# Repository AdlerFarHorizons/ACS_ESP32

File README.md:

# ACS_ESP32
### Current State of ACS Development (April 2022)

The Altitude Control System has been updated to work with the ESP32 Microcontroller which has enabled wireless file sharing via WiFi. The exact module is the **DOIT ESP32 DEVKIT V1**. 

**Firmware**

The [ACS_ESP32 Code](https://github.com/AdlerFarHorizons/ACS_ESP32) has been organized for clarity, usage, and further development. The code now lives publicly within the [Adler Far Horizons GitHub](https://github.com/AdlerFarHorizons). Additionally, the code and the libraries are packaged by the [PlatformIO](https://platformio.org/platformio-ide) package, which runs within [VS Code](https://code.visualstudio.com/), and should be used to maintain and update the code. Cloning the repository from within GitHub will ensure PlatformIO compiles the code properly. 

The following are updates to the code:

- Code has been organized into separate header files (_name_.h) so as to keep all related code for specific peripherals in separate files. This allows the programmer to quickly find specific functions.
- Wireless file retrieval has been added. The microcontroller will broadcast a hotspot with SSID: “ACS SD-CARD”. The SD Card content can be displayed by entering the IP-ADDRESS: “192.168.4.1” into a web browser after establishing wifi connection. 

To access wifi settings, 

1. Turn on the ACS by using the Toggle ON/OFF switch or by plugging using a USB cable.

2. Using your computer (or mobile device), look for the “ACS SD-Card” Hotspot under the WIFI settings. You do not need a password to access the hotspot.

3. Identify the 3-position switch on the ACS Faceplate. Place this switch to the Closed Position (or the center position), and Press the Button as indicated on the Display. You should now see the IP Address displayed, which should be “192.168.4.1”.

   1. Sometimes the connection is poor, and you may need to bring the ACS closer to you, or you may need to reestablish the WIFI connection by turning off/on your wireless antenna on your computer/mobile device.

4. If your connection is established, you should now see a window as shown below: 

Within this window you may browse through the content within the SD Card by selecting Directory. If you wish to download a file, you can copy/paste the full name of the file and paste it into the Downloads prompt window. 

The use of WIFI is to be able to download the param.txt file, edit it and upload it back into the ACS SD Card. Additionally, one can download the datalog.csv, which contains all the flight ACS data. Ideally, one should not have to remove the SD Card from the board. 

__Note: I’ve noticed that deleting a file via WIFI sends it to the .Trash Folder. It doesn’t fully delete the file. So when the script runs and looks for a file within the list of files, if the file exists within the .Trash folder, then the code will send a True that the file exists. The code either needs a exception to not search within .Trash or a “Permanently Delete” function that deletes the content within .Trash.__

### Design Files, Notes, and Code

[GitHub - ACS_ESP32](https://github.com/AdlerFarHorizons/ACS_ESP32)

[Google Drive: System Redesign Concept 2021/22](https://drive.google.com/drive/folders/1W37AFGbH8UgUThIRDDYVn1NRzvqxMLDn)

- [PCB Design Files](https://drive.google.com/drive/folders/1NPGxpG3kCgMrHuZ5ZHsxEYcvnIpvRIrO?usp=sharing)
- [PCB Schematic PDF](https://drive.google.com/file/d/19PMDI1tQQiT3bByivIbot_-rFZreG9Ll/view?usp=sharing)

[Purchase Materials****](https://docs.google.com/spreadsheets/d/1xs60UxvHJ-fiQykCOm7pP0R7RBD7VAjFjShzD04MD6w/edit#gid=0)

**Compiling using Arduino**

To compile and upload the script file using Arduino, you must install the ESP32 Arduino Boards using instructions found here.

**Instructions**: [Installing ESP32 in Arduino IDE](https://randomnerdtutorials.com/installing-the-esp32-board-in-arduino-ide-windows-instructions/) 

Upon Install, select the **DOIT ESP32 DEVKIT V1 **Board from the drop down menu within **Tools/Board/ESP32 Arduino/. **The this dropdown menu is shown below:

**Printed Circuit Board (PCB)**

The PCB for the ACS has had several modifications. Primarily, the Teensy 3.6 Microcontroller has been exchanged for the WIFI capable microcontroller [**ESP-WROOM-32 ESP-32S Development Board**](https://www.amazon.com/dp/B08D5ZD528?psc=1&ref=ppx_yo2ov_dt_b_product_details)**. **This microcontroller does not include an SD Card Reader, which is why an [SD Card Reader Breakout Board](https://www.sparkfun.com/products/13743) has been added to the new design. 

In addition to the microcontroller modifications, the PCB now utilizes a few surface-mounted devices. 

- **Power**: The previous design used the [LM7805 Voltage Regulator](https://www.sparkfun.com/datasheets/Components/LM7805.pdf) which dropped the 7.2V to 5V using a conventional heat dissipation voltage regulator. This approach worked, but consumed much higher current draw. Therefore, the DC-DC voltage regulator was exchanged for a low-dropout voltage regulator. The selected voltage regulator is now the [MC33269](https://www.onsemi.com/pdf/datasheet/mc33269-d.pdf). 
- **Logic Level Shifter: The original [4-channel I2C-safe Bi-directional Logic Level Converter - BSS138](https://www.adafruit.com/product/757) has been stripped down to only use 1 of the [BSS138](https://www.onsemi.com/pdf/datasheet/bss138-d.pdf) configured to convert signals from low voltage 3V3 to 5.0 Volts.**
- **Actuator**: The current actuator is the L12-50-210-6-R, which runs a servo motor to extend the actuator. However, this actuator does not provide feedback positional data, therefore the recommendation is to upgrade the actuator to the [**L12-50-210-6-I**](https://s3.amazonaws.com/actuonix/Actuonix+L12+Datasheet.pdf)**. **The L12-I version contains an integrated microcontroller which allows the user to obtain positional feedback data. 

**Connection Diagram**

**AA Battery Set for Actuator + Primary Board**

The current AA battery set used in the ACS is the [ Xeno XL-060F AA 2400mAh 3.6V Lithium Thionyl Chloride (LiSOCI2)](https://www.batteryjunction.com/xl-060f-xeno-aa.html) \[[datasheet](https://files.batteryjunction.com/frontend/files/xeno/datasheet/Xeno-XL-060F-Datasheet.pdf)], which is placed in Series to increase the voltage to 7.2. The ACS uses four (4) AA Batteries - 2 sets in Series, and those two sets are merged in parallel to increase the capacity (mAh).

**External Temperature Battery Board**

This board has been prepared to connect to the primary board, but is placed separately from it in order to be close enough to the heating elements for it to monitor temperatures and hold the two 9V batteries to power the heating element.

- **Temperature:** The temperature is monitored using a [DS18B20 Digital Thermometer](https://datasheets.maximintegrated.com/en/ds/DS18B20.pdf).
- **Batteries:** The 9V batteries are held in place by both the structure of the compartment it will reside in and power the heating through two [5331TR (Leaf-Spring Battery Contacts)](https://www.digikey.com/en/products/detail/keystone-electronics/5331TR/8347168?utm_adgroup=General&utm_source=google&utm_medium=cpc&utm_campaign=Smart%20Shopping_Product_Zombie%20SKUS&utm_term=&utm_content=General&gclid=CjwKCAiAprGRBhBgEiwANJEY7DhVwsQ1aTq7gBAcb5RRHrVmZTxuCmMAlXrXpHnIgzOPE_fwFTYqjRoCqlUQAvD_BwE) each. These battery contacts serve a dual purpose as the screws that will go through them are the same ones being used to mount the board securely.
- **Connection: The board is connected to the primary one using a 5 Pin [Screw Terminal Block](https://www.pololu.com/product/2493) affixed to the bottom of the board which will allow wires to be led through a hole beneath it on the way to the main board.**

****

### NEXT TASKS

**Actuator**

- After providing 6.5V to the L-12-I actuator via the DC-Power Supply, **ensure the actuator responds correctly to the ACS_ESP32 Code**. If it does not respond correctly, change the RC_INPUT_SIG Pin to another pin on the ESP32. I’ve identified that some of the pins on the ESP32 seem to short out the microcontroller and/or do not behave as intended. On the code, navigate to actuator.h and find line “**int actuator_pin = 17;”.** Test out a different GPIO pio, upload code, and test for actuator response. 

  - If the actuator ‘jerks’ back and forth when attempting to reach a certain position, the datasheet recommends to “place a 1–4Ω resistor in series with the actuator’s red V+ lead wire”.

- **Actuator Feedback** via the POS_FEEDBACK_SIG pin, which has been connected to GPIO13, must be checked for incoming data. After declaring the POS_FEEDBACK_PIN as an int, use pinMode(POS_FEEDBACK_PIN, INPUT); to initialize the pin on the microcontroller, one should be able to read the voltage using the analogRead() function. One should expect a voltage reading from 0-255, which then can be mapped using map() to correspond to a percentage. 

- Actuator Pins CURR_INPUT_SIG and VOLT_INPUT_SIG have purposefully been disconnected from the microcontroller. These features for controlling the actuator are unnecessary as the actuator will be controlled via the RC_INPUT_SIG.

**The Heating Element**

- The Heating Element needs to be tested the new downsize of voltage output. Originally the heating element uses 3 batteries in series of 9V totalling 27V. Now, the downsize should yield 18V. This downsize has been considered given the usage of an aluminum pipe for heat distribution. 
- Code: Create Algorithm to measure heat transfer between the heating element and the internal electronics, by measuring the temperature outside the heating element (battery board) and the internal Pressure Sensor thermometer. Using these temperatures, create a function that activates the heating element below a specific temperature, and conversely deactivates the heating element when temperatures reach a specific maximum. 
- Heating Element Transistor 2N2222 schematic needs to be tested prior to finalizing the schematic design of the primary board. 

Above: Circuit concept idea for the resistor being the heating element connected to one end of the transistor 2N2222.

Above: Schematic capture of the heating element connector. Here the heating element is connected to one side of the NPN transistor. The Base is connected to the microController, and the Collector is connected to the negative end of the 9V battery set, which is connected in series. 

**Code**

Within the void setup() function, ensure that when the sd_setup() does not create a new file each time the boot process occurs. The ACS should conserve and append the currently existing logfile if it exists. If the file does not exist, the code is instructed to write the parameters below:

else
{ unsigned long size = logFile.size();
  Serial.print("Filesize: "); Serial.println(size);
  delay(5000);
  if (size < 500){
    display.clearDisplay();
    display.println("Creating new File");
    display.display();
    delay(5000);

    String log = 
                "Far Horizons | Adler Planetarium" + String("\n") + 
                "Flight Number: " + "," +            String(flightNum) + "\n" + 
                "Firmware: " + "," +                  String(the_sketchname) + "\n" + 
                "Compiled on: " +  "," +               String(__DATE__) +  " at " +  String(__TIME__) + "\n" +
                "Venting Altitude (m): " + "," +      String(VENT_ALT) + "\n" + 
                "Float Time (min): " + "," +          String(FLOAT_TIME) + "\n" + 
                "Max Float Altitude (m): " + "," +   String(MAXFLOATALT) + "\n" + 
                "Release Position %: " + "," +        String(RELEASE_POS) + "\n" + 
                "Venting Position %: " + "," +        String(OPEN_POS) + "," + 
                "Closed Position" + "," + String(CLOSED_POS) + "\n";

Currently this section of the code does not work as intended. Instead, the code creates a new file and does not append the parameters found above.

**ACS Primary PCB**

- Label Pins on Connectors using layer tNames and bNames.
- Ensure Connector are placed in the correct location to help diminish excess wire routing and unnecessary wire-curvatures.
- Rework routes after device placement and use ratsnest to create the correct ground plane

**Currently Wired Diagram on Breadboard: **

**Full Schematic Diagram with External Temp Board**

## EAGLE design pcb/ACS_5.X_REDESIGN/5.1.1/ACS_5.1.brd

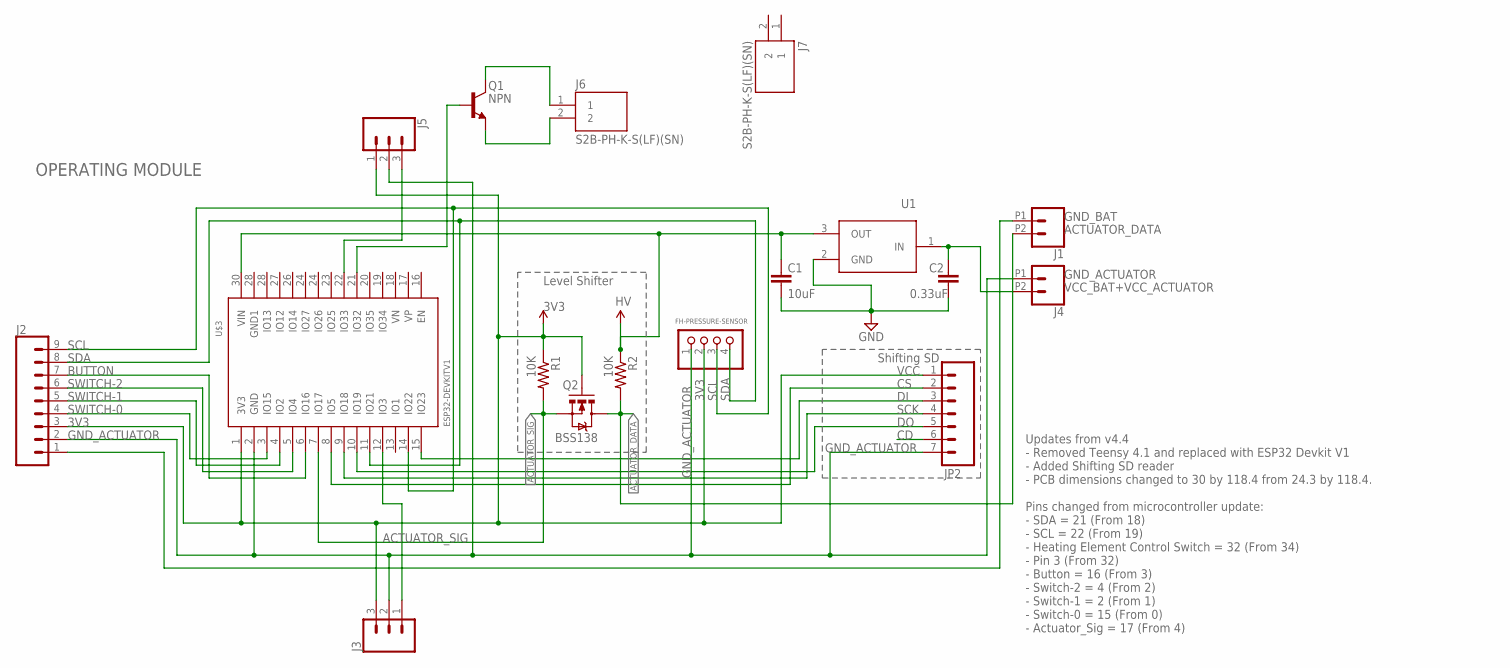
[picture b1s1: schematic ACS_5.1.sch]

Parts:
C1: 10uF; CAPC1608X85
C2: 0.33uF; CAPC1608X85
FH-PRESSURE-SENSOR: PINHD-1X4; 1X04
J1, J4: CONN_022.54MM_SCREWTERM; 1X02_2.54_SCREWTERM
J2: CONN_09; 1X09
J3, J5: CONN_03; 1X03
J6, J7: S2B-PH-K-S(LF)(SN); JST_S2B-PH-K-S(LF)(SN)
JP2: M07; 1X07
Q1: NPN; SOT95P237X112-3N
Q2: BSS138; SOT23-3
R1, R2: 10K; 0603-RES
U1: MC78M05BDTRKG
U$3: ESP32DEVKITV1; ESP32-DEVKITV1

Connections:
3V3: FH-PRESSURE-SENSOR.2, J2.3, J3.3, J5.1, JP2.1, Q2.1 (G), R1.1, U$3.1 (3V3)
ACTUATOR_DATA: J1.P2 (2), Q2.3 (D), R2.2
ACTUATOR_SIG: Q2.2 (S), R1.2, U$3.7 (IO17)
BUTTON: J2.7, U$3.6 (IO16)
GND: C1.2, C2.2, U1.2 (GND)
GND_ACTUATOR: FH-PRESSURE-SENSOR.1, J2.2, J3.2, J4.P1 (1), J5.2, JP2.7, U$3.2 (GND)
GND_BAT: J1.P1 (1), J2.1
HV: C1.1, R2.1, U1.3 (OUT), U$3.30 (VIN)
unnamed: J5.3, U$3.22 (IO33)
unnamed: J6.1, Q1.3 (C)
unnamed: J6.2, Q1.1 (E)
unnamed: Q1.2 (B), U$3.21 (IO32)
unnamed: J3.1, U$3.12 (IO3)
unnamed: JP2.3, U$3.15 (IO23)
unnamed: JP2.2, U$3.8 (IO5)
unnamed: JP2.4, U$3.9 (IO18)
unnamed: JP2.5, U$3.10 (IO19)
SCL: FH-PRESSURE-SENSOR.3, J2.9, U$3.14 (IO22)
SDA: FH-PRESSURE-SENSOR.4, J2.8, U$3.11 (IO21)
SWITCH-0: J2.4, U$3.3 (IO15)
SWITCH-1: J2.5, U$3.4 (IO2)
SWITCH-2: J2.6, U$3.5 (IO4)
VCC_BAT+VCC_ACTUATOR: C2.1, J4.P2 (2), U1.1 (IN)

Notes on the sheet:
OPERATING MODULE
Level Shifter
Updates from v4.4 - Removed Teensy 4.1 and replaced with ESP32 Devkit V1 - Added Shifting SD reader - PCB dimensions changed to 30 by 118.4 from 24.3 by 118.4. Pins changed from microcontroller update: - SDA = 21 (From 18) - SCL = 22 (From 19) - Heating Element Control Switch = 32 (From 34) - Pin 3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
SCK
VCC
Shifting SD

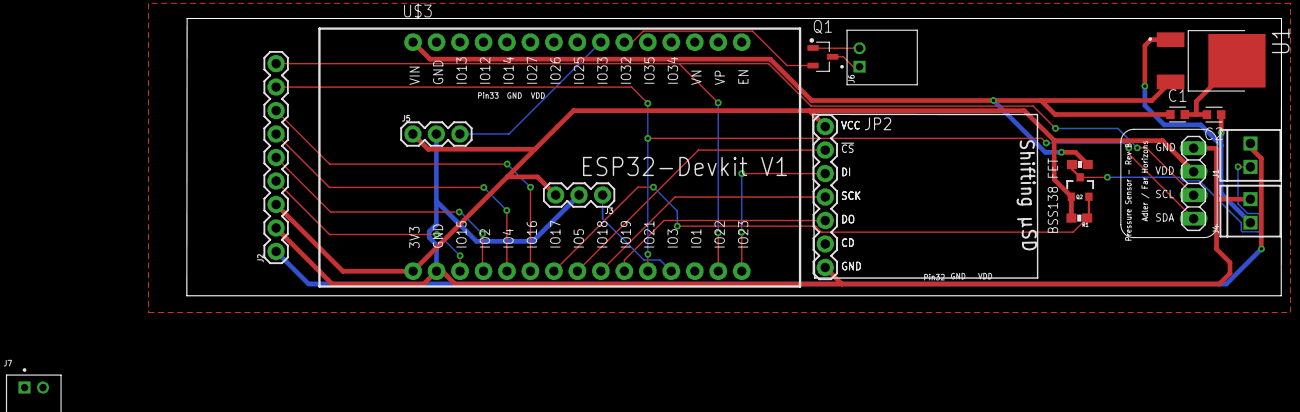
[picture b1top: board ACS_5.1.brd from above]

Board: 2 copper layers, 118.4 x 30.0 mm, 17 parts (0 on the bottom side), 23 nets.

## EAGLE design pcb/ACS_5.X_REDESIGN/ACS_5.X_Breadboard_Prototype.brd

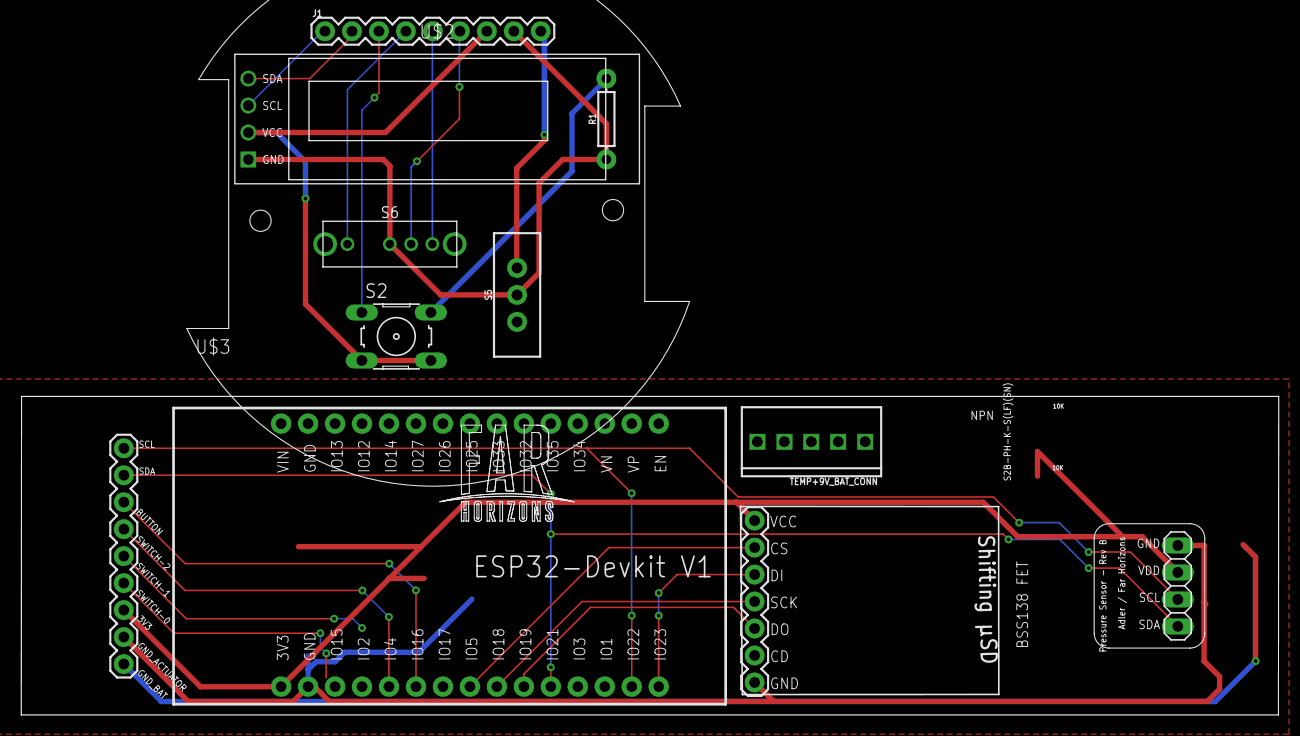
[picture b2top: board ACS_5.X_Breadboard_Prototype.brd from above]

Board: 2 copper layers, 118.4 x 30.0 mm, 11 parts (0 on the bottom side), 15 nets.

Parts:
FH-PRESSURE-SENSOR: 1X04
J1, J2: 1X09
JP2: 1X07
R1: 1k; AXIAL-0.3
S2: B3F-10XX
S5: SWITCH_SPDT_PTH_11.6X4.0MM
S6: OS103011MS8QP1; OS102011MS8QP1
TEMP+9V_BAT_CONN: SCREW_TERM_1X05_2.54; 1X05_2.54_SCREWTERM
U$2: DISPLAY-OLED-128X32
U$3: ESP32DEVKITV1; ESP32-DEVKITV1

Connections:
3V3: FH-PRESSURE-SENSOR.2, J1.7, J2.3, JP2.1, S2.3, S2.4, TEMP+9V_BAT_CONN.P5, U$2.2, U$3.1
BUTTON: J1.3, J2.7, S2.1, U$3.6
EXT_TEMP_SIG: TEMP+9V_BAT_CONN.P4, U$3.23
GND: FH-PRESSURE-SENSOR.1, J1.8, J2.1, J2.2, JP2.7, R1.P$1, S5.2, S6.2, TEMP+9V_BAT_CONN.P3, U$2.1, U$3.2
unnamed: R1.P$2, S2.2
unnamed: J1.9, S5.1
unnamed: JP2.3, U$3.15
unnamed: JP2.2, U$3.8
unnamed: JP2.4, U$3.9
unnamed: JP2.5, U$3.10
SCL: FH-PRESSURE-SENSOR.3, J1.1, J2.9, U$2.3, U$3.14
SDA: FH-PRESSURE-SENSOR.4, J1.2, J2.8, U$2.4, U$3.11
SWITCH-0: J1.6, J2.4, S6.3, U$3.24
SWITCH-1: J1.5, J2.5, S6.4, U$3.24
SWITCH-2: J1.4, J2.6, S6.1, U$3.5

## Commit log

2022-03-16 development
2022-03-16 Description
2022-03-16 cleaned
2022-03-17 libs
2022-03-26 wifi-module working
2022-03-26 SSDI Updates
2022-03-28 Dallas Temp Integration
2022-03-28 Change: File Appen in main
2022-04-12 Update Webpage Functionality
2022-04-14 Update Pin no. for ESP32
2022-04-18 SpellCheck
2022-04-18 new file
    new file
2022-04-18 folder_update
2022-04-18 adding pcb
2022-04-18 git_mod
2022-04-19 Update README.md
    image update

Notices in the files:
parts and their libraries:
SparkFun-Connectors: Licensing: Creative Commons ShareAlike 4.0 International - https://creativecommons.org/licenses/by-sa/4.0
SparkFun-Connectors: Licensing: CC v3.0 Share-Alike You are welcome to use this library for commercial purposes.
